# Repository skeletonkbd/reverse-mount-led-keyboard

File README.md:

# リバースマウント LED3 種つけ比べキーボード

バックライトにリバースマウント可能な LED3 種類を採用したキーボード基板です。はんだ付けの難易度はかなり高めだと思います。

# BOM

| 製造元部品番号  | 種別            | 個数 |
| --------------- | --------------- | ---- |
| SK6812MINI-E    | LED             | 3    |
| SK6812D-EC3210R | LED             | 3    |
| WS2812C-2020    | LED             | 3    |
| 1N4148W         | Switching Diode | 9    |
| Pro Micro       | -               | 1    |
| TS-1136-4.3     | Switch          | 1    |

# Build Guide

## 1. 部品実装

LED の向きは以下のとおりです。

## 2. ファームウェアの書き込み

ファームウェアは [こちら](/firmware)をご利用ください。

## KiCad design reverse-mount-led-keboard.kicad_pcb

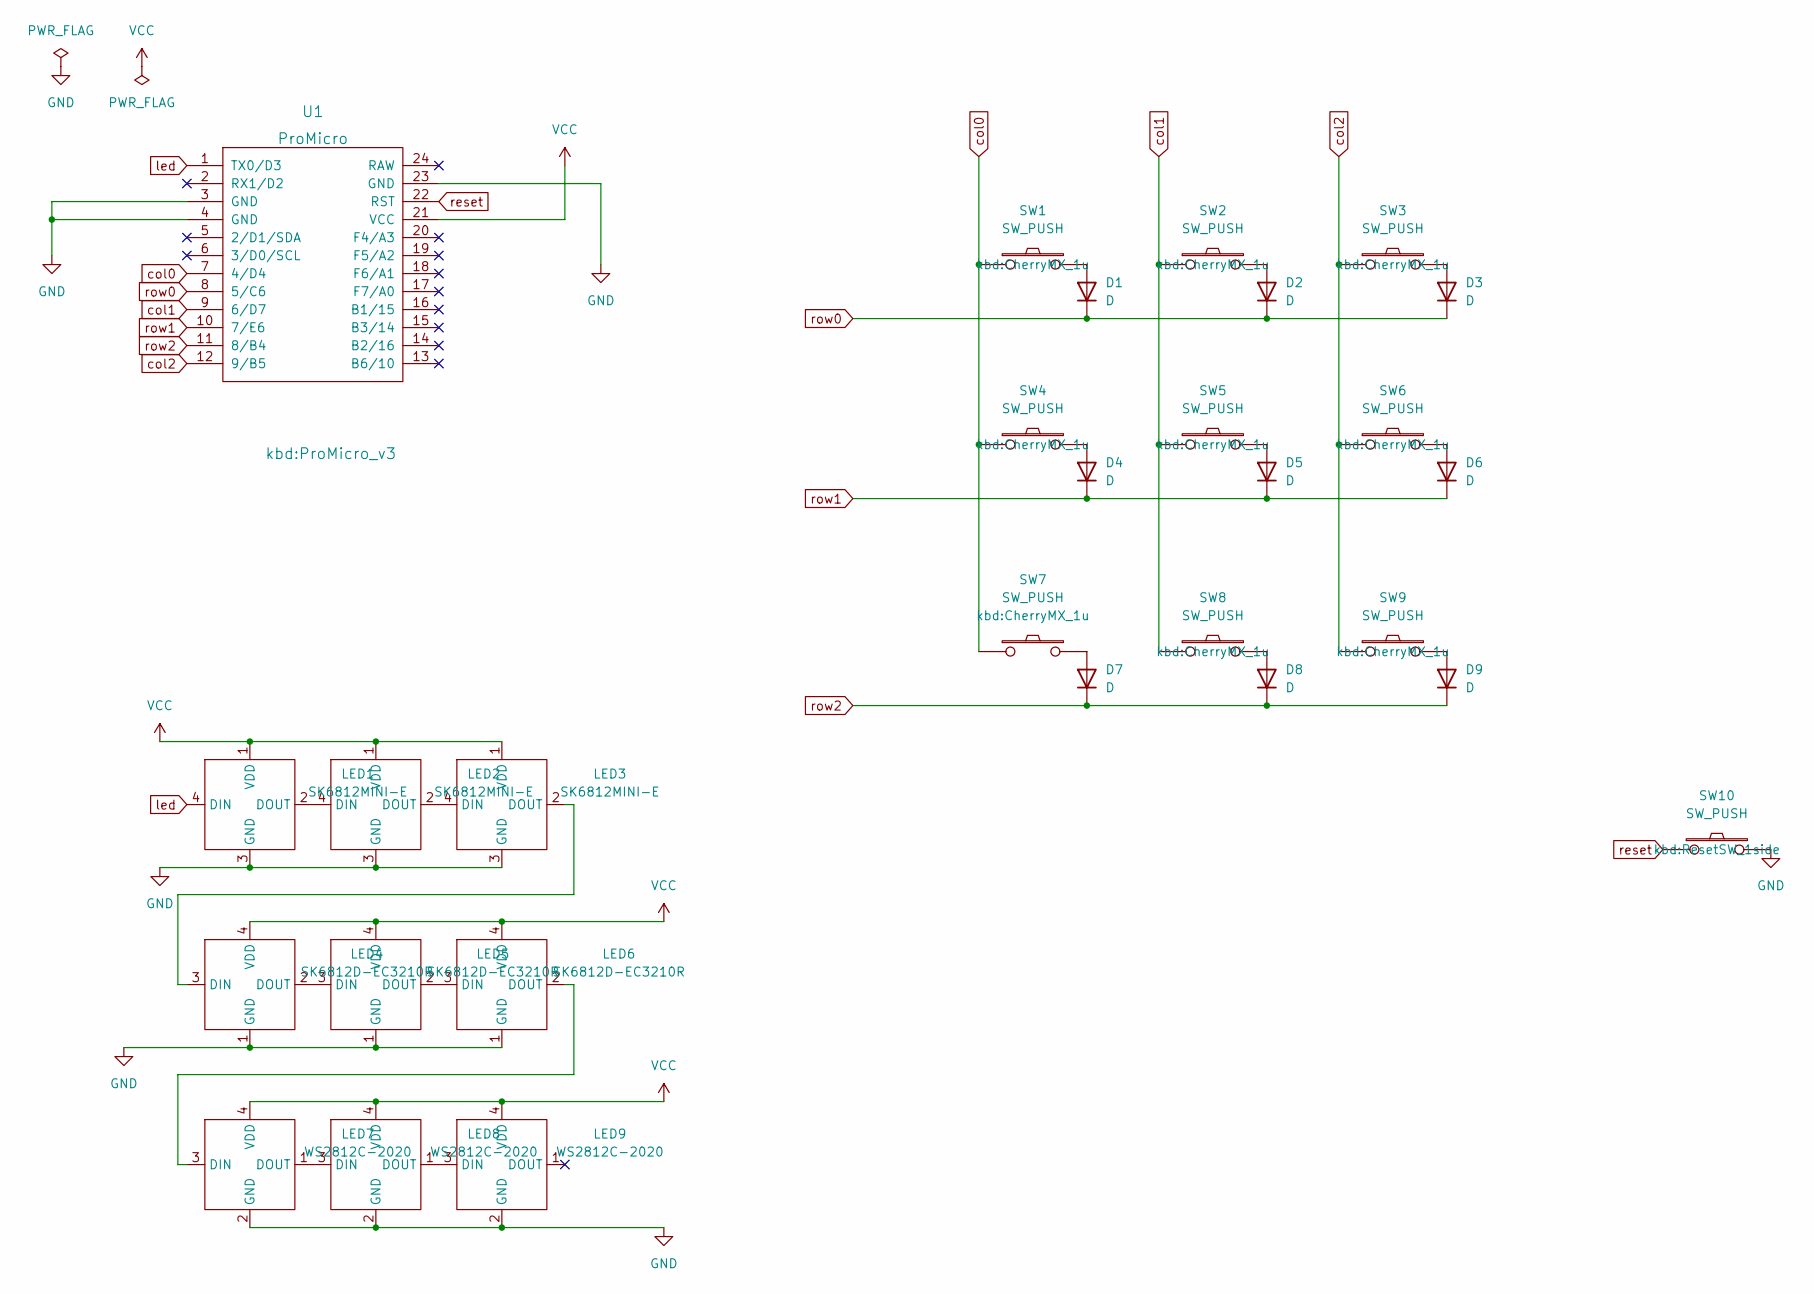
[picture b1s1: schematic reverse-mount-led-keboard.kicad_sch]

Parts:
D1, D2, D3, D4, D5, D6, D7, D8, D9: D; D3_SMD_v2; LCSC C81598
LED1, LED2, LED3: SK6812MINI-E
LED4, LED5, LED6: SK6812D-EC3210R
LED7, LED8, LED9: WS2812C-2020
SW1, SW2, SW3, SW4, SW5, SW6, SW7, SW8, SW9: SW_PUSH; CherryMX_1u
SW10: SW_PUSH; ResetSW_1side; LCSC C455263
U1: ProMicro; ProMicro_v3

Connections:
GND: LED1.3 (GND), LED2.3 (GND), LED3.3 (GND), LED4.1 (GND), LED5.1 (GND), LED6.1 (GND), LED7.2 (GND), LED8.2 (GND), LED9.2 (GND), SW10.2, U1.3 (GND), U1.4 (GND), U1.23 (GND)
unnamed: D1.2 (A), SW1.2
unnamed: D4.2 (A), SW4.2
unnamed: D5.2 (A), SW5.2
unnamed: D6.2 (A), SW6.2
unnamed: D7.2 (A), SW7.2
unnamed: D8.2 (A), SW8.2
unnamed: D9.2 (A), SW9.2
unnamed: LED1.2 (DOUT), LED2.4 (DIN)
unnamed: LED2.2 (DOUT), LED3.4 (DIN)
unnamed: LED3.2 (DOUT), LED4.3 (DIN)
unnamed: LED4.2 (DOUT), LED5.3 (DIN)
unnamed: LED5.2 (DOUT), LED6.3 (DIN)
unnamed: LED6.2 (DOUT), LED7.3 (DIN)
unnamed: LED7.1 (DOUT), LED8.3 (DIN)
unnamed: LED8.1 (DOUT), LED9.3 (DIN)
unnamed: D2.2 (A), SW2.2
unnamed: D3.2 (A), SW3.2
VCC: LED1.1 (VDD), LED2.1 (VDD), LED3.1 (VDD), LED4.4 (VDD), LED5.4 (VDD), LED6.4 (VDD), LED7.4 (VDD), LED8.4 (VDD), LED9.4 (VDD), U1.21 (VCC)
col0: D1.1 (K), D2.1 (K), D3.1 (K), U1.8 (5/C6)
col1: D4.1 (K), D5.1 (K), D6.1 (K), U1.10 (7/E6)
col2: D7.1 (K), D8.1 (K), D9.1 (K), U1.11 (8/B4)
led: LED1.4 (DIN), U1.1 (TX0/D3)
reset: SW10.1, U1.22 (RST)
row0: SW1.1, SW4.1, SW7.1, U1.7 (4/D4)
row1: SW2.1, SW5.1, SW8.1, U1.9 (6/D7)
row2: SW3.1, SW6.1, SW9.1, U1.12 (9/B5)

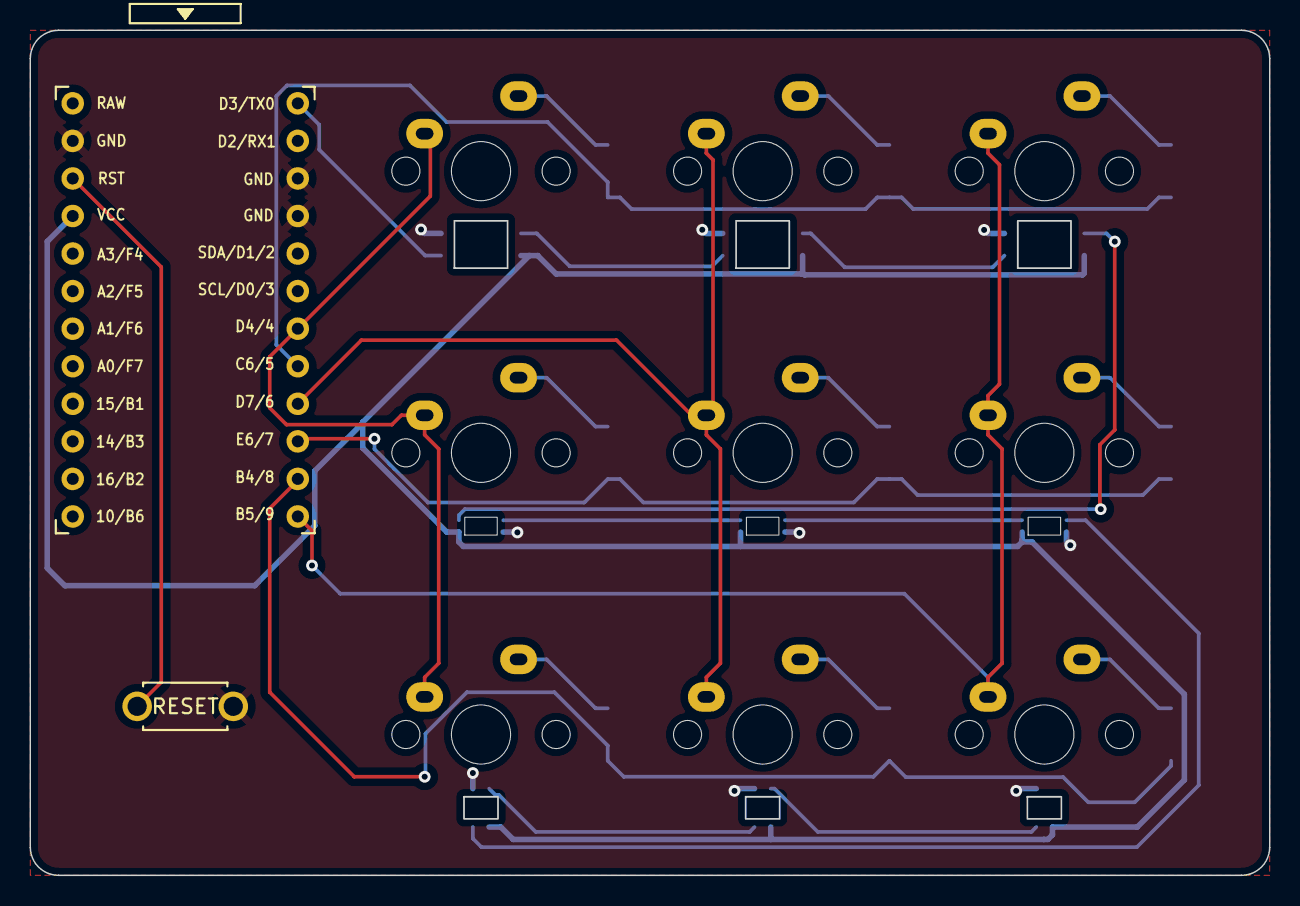
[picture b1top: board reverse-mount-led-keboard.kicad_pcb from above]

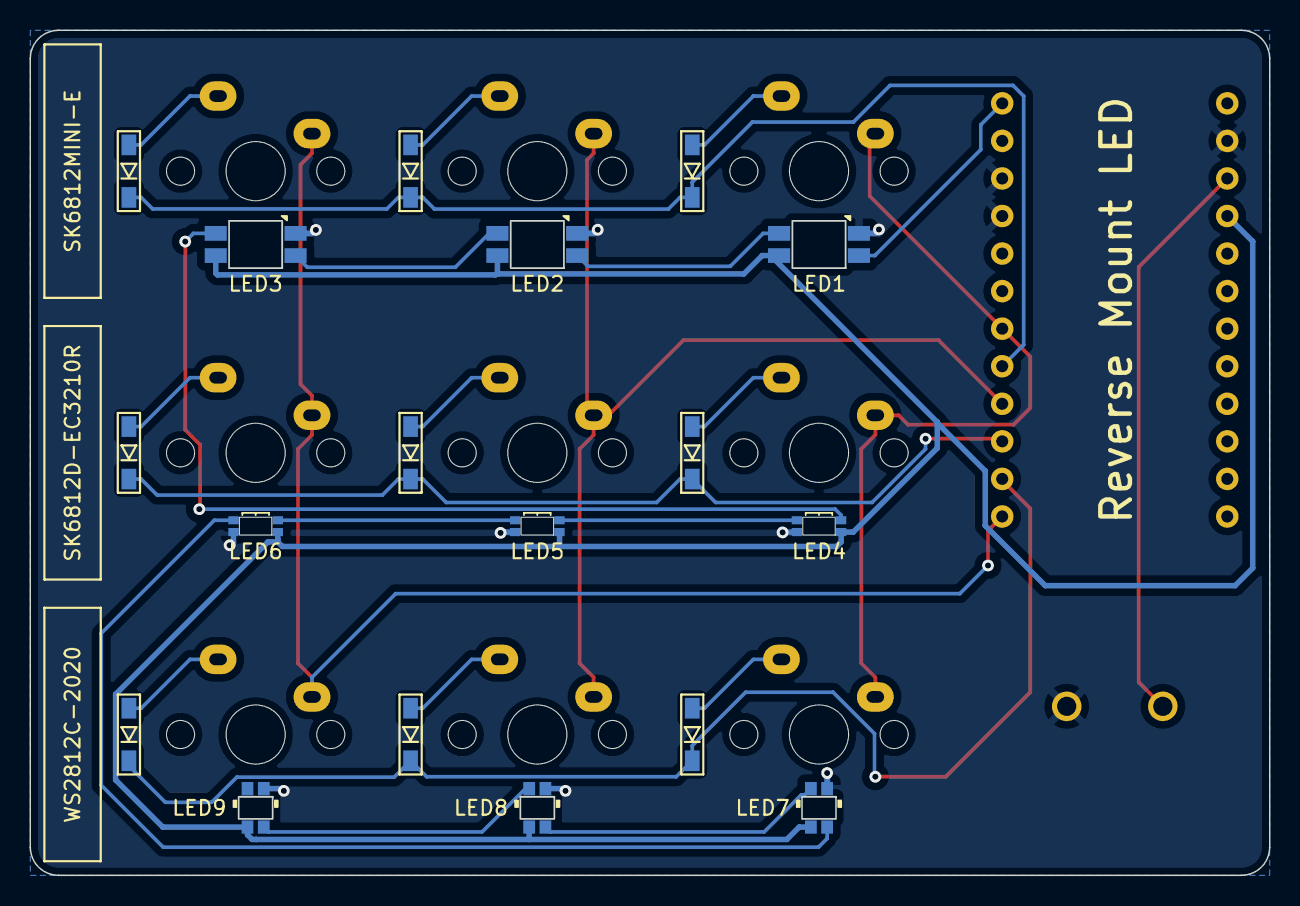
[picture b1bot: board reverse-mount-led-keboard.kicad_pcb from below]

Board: 2 copper layers, 83.8 x 57.1 mm, 29 parts (18 on the bottom side), 27 nets.

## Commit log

2022-06-18 init
2022-06-18 readme
2022-07-07 add firmware
2022-07-08 add build guide & fix firmware
